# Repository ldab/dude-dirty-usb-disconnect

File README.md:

# dude-dirty-usb-disconnect

USB CDC-ACM uart like controlled USB Hub:

- 1.5A fuse;
- Power switch with overcurrent, undervoltage and overtemperature protection;
- ESD Protection diodes on the USB lines;

## Todo

- [ ] WebBle
- [ ] Web flasher, like: https://esphome.github.io/esp-web-tools/ (does it work over CDC?)
- [ ] Get a PID from https://pid.codes/howto/ (only found how to change TinyUSB PID)
- [ ] There is some overflow around the help print for the `hub_settings`
- [ ] 3D printed case
- [x] `sdkconfig.default` for release with CDC (no jtag)

## Why?

I needed something to remotely disconnect and reconnect an USB device from my workstation, aka managed USB hub, the commercially available options where either [expensive](https://www.usbgear.com/managed-hubs.html) or needed [drivers](https://www.yepkit.com/products/ykush). So the idea here is an device that does not need external power and works as a USB CDC-ACM and one can simply send `hub_ports_off` over the terminal to turns the USB ports off.

## How?

As per USB-C [standard](https://www.usb.org/sites/default/files/USB%20Type-C%20Spec%20R2.0%20-%20August%202019.pdf), if you are bored read section 4.6.2.1, an USB-C source device should at least source 1.5A, as it is written:

  > All exposed USB Type-C Current ports shall have the ability to offer the same power capabilities. 
  > - All ports shall initially offer 1.5 A.

With that being said we can use the HUB with USB2.0 devices (500mA) with no problems. The device monitor the CC pins and it can detect if the source is able to provide the minimum required current (1.5A):

**Table 4-36** indicates that a minimum of 0.7V should be read on CC for a 1.5A capable source, so we should be good with a USB-C to USB-C cable.

If you have an old laptop like me and it does not have an USB-C port, one can override the source check and send `hub_setings override_cc 1` and the HUB ports will be enabled even if the source does not provide enough power. On that case you may experience some weirdness on the final USB device, but hey, if you are here, you should have some idea of what you are doing.

One can also issue `hub_status` and see what the status is, for example:

```
dirty_usb_disconnect> hub_status
FW version: v0.0.1a
Hub is: Enabled
Fault: None
USB Host does not provide 1.5A
```

The CDC-ACM USB driver is based on espressif [example](https://github.com/espressif/esp-idf/tree/v5.2.1/examples/system/console/basic), you will find how it works there... the PID is 0x303A and VID is 0x0009. In case you are building the `debug` version the output will be over the USB-JTAG controller, PID:VID 0x303A:0x1001 (here you can also debug over USB, cool :smile:)

## Firmware

### Available commands

* Type `help` on the terminal

### LED

* Blue - idle, ports off;
* Green - ports on;
* Red - fault;

## Hardware 

- 1.5A fuse;
- [TPS2065C](https://www.ti.com/product/TPS2065C): 1A load, 86mΩ USB power switch with overcurrent, undervoltage and overtemperature protection;
- Device itself draws ~40mA;

- On the boards I made I changed all the resistors to 5.1KOhms for simplicity, the schematic did not update;
- Jumper 1 allows to use the HUB without crystal, saving 0.05USD :smile:;
- Jumper 2 and 3 changes the ADC to channel 2 as the channel 1 has a boot glitch (it should be ok). Bear in mind that ADC2 does not work with WiFi (rtfm);

## Note

- The hub controller datasheet indicates a internal pullup on RST, but it seems something is going on there, so next revision needs an external pull up, for now: https://github.com/ldab/dude-dirty-usb-disconnect/blob/4d217c8b5ad06fc77f75e4162ce3a6a554248eb0/components/app_hub_control/app_hub_control.c#L406

## Outro

- Some 3D models from: www.3dcontentcentral.com

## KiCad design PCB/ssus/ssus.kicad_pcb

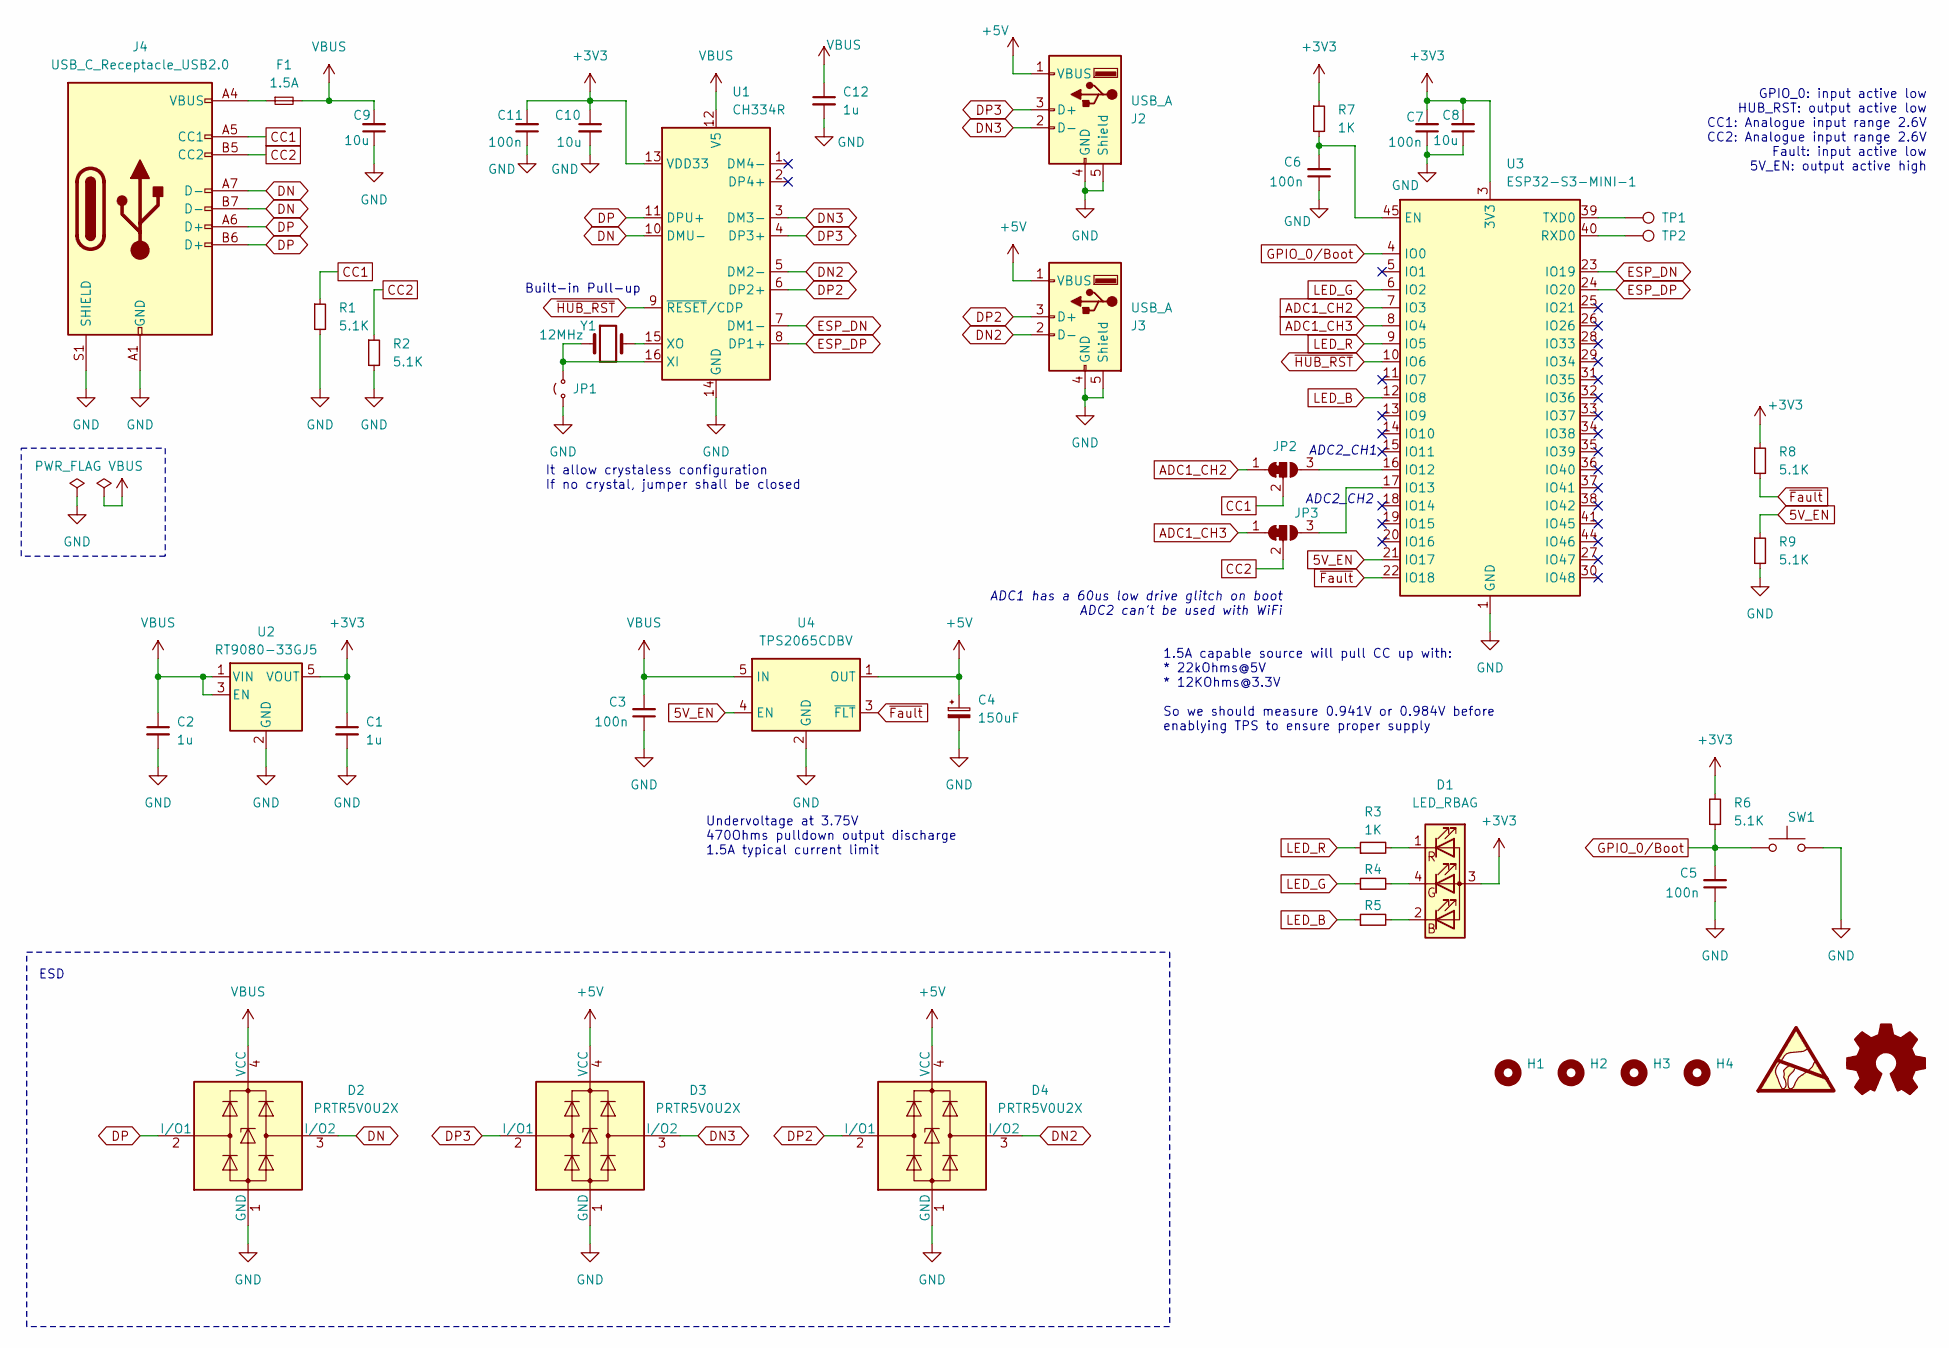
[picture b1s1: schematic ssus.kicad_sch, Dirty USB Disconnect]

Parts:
C1, C2, C12: 1u; C_0603_1608Metric; LCSC C1592
C3, C5, C6, C7, C11: 100n; C_0603_1608Metric; LCSC C338036
C4: 150uF; C_Elec_6.3x5.4; LCSC C2895744
C8, C9, C10: 10u; C_0603_1608Metric; LCSC C87152
D1: LED_RBAG; LED_Cree-PLCC4_2x2mm_CW; LCSC C108793
D2, D3, D4: PRTR5V0U2X; SOT-143; LCSC C12333
F1: 1.5A; Fuse_1206_3216Metric; LCSC C89655
H1, H2, H3, H4: MountingHole; MountingHole_2.1mm
J2, J3: USB_A; USB_A_TE_292303-7_Horizontal; LCSC C42641
J4: USB_C_Receptacle_USB2.0; USB_C_Receptacle_HRO_TYPE-C-31-M-12; LCSC C319148
JP1: 2; SolderJumper-2_P1.3mm_Open_RoundedPad1.0x1.5mm
JP2, JP3: 3; SolderJumper-3_P1.3mm_Bridged12_RoundedPad1.0x1.5mm
R1, R2, R6, R8, R9: 5.1K; R_0603_1608Metric; LCSC C14677
R3, R4, R5, R7: 1K; R_0603_1608Metric; LCSC C384295
SW1: SW_Push; SW_Push_1P1T_NO_CK_KMR2; LCSC C128941
TP1, TP2: TestPoint; TestPoint_Pad_D1.5mm
U1: CH334R; QSOP-16_3.9x4.9mm_P0.635mm; LCSC C4154405
U2: RT9080-33GJ5; SOT-23-5; LCSC C841192
U3: ESP32-S3-MINI-1; ESP32-S2-MINI-1; LCSC C2913206
U4: TPS2065CDBV; SOT-23-5; LCSC C353882
Y1: 12MHz; Oscillator_SMD_ECS_2520MV-xxx-xx-4Pin_2.5x2.0mm; LCSC C21714041

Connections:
5V_EN: R9.1, U3.21 (IO17), U4.4 (EN)
+3V3: C1.1, C7.2, C8.2, C10.1, C11.2, D1.3 (A), R6.2, R7.1, R8.1, U1.13 (VDD33), U2.5 (VOUT), U3.3 (3V3)
+5V: C4.1, D3.4 (VCC), D4.4 (VCC), J2.1 (VBUS), J3.1 (VBUS), U4.1 (OUT)
ADC1_CH2: JP2.1 (A), U3.7 (IO3)
ADC1_CH3: JP3.1 (A), U3.8 (IO4)
CC1: J4.A5 (CC1), JP2.2 (C), R1.1
CC2: J4.B5 (CC2), JP3.2 (C), R2.1
DN: D2.3 (I/O2), J4.A7 (D-), J4.B7 (D-), U1.10 (DMU-)
DN2: D4.3 (I/O2), J3.2 (D-), U1.5 (DM2-)
DN3: D3.3 (I/O2), J2.2 (D-), U1.3 (DM3-)
DP: D2.2 (I/O1), J4.A6 (D+), J4.B6 (D+), U1.11 (DPU+)
DP2: D4.2 (I/O1), J3.3 (D+), U1.6 (DP2+)
DP3: D3.2 (I/O1), J2.3 (D+), U1.4 (DP3+)
ESP_DN: U1.7 (DM1-), U3.23 (IO19)
ESP_DP: U1.8 (DP1+), U3.24 (IO20)
GND: C1.2, C2.2, C3.1, C4.2, C5.1, C6.1, C7.1, C8.1, C9.1, C10.2, C11.1, C12.2, D2.1 (GND), D3.1 (GND), D4.1 (GND), J2.4 (GND), J2.5 (Shield), J3.4 (GND), J3.5 (Shield), J4.A1 (GND), J4.A12 (GND), J4.B1 (GND), J4.B12 (GND), J4.S1 (SHIELD), JP1.1 (A), R1.2, R2.2, R9.2, SW1.2, U1.14 (GND), U2.2 (GND), U3.1 (GND), U3.2 (GND), U3.42 (GND), U3.43 (GND), U3.46 (GND), U3.47 (GND), U3.48 (GND), U3.49 (GND), U3.50 (GND), U3.51 (GND), U3.52 (GND), U3.53 (GND), U3.54 (GND), U3.55 (GND), U3.56 (GND), U3.57 (GND), U3.58 (GND), U3.59 (GND), U3.60 (GND), U3.61 (GND), U3.62 (GND), U3.63 (GND), U3.64 (GND), U3.65 (GND), U4.2 (GND)
GPIO_0/Boot: C5.2, R6.1, SW1.1, U3.4 (IO0)
LED_B: R5.1, U3.12 (IO8)
LED_G: R4.1, U3.6 (IO2)
LED_R: R3.1, U3.9 (IO5)
unnamed: D1.2 (BK), R5.2
unnamed: D1.4 (GK), R4.2
unnamed: D1.1 (RK), R3.2
unnamed: F1.1, J4.A4 (VBUS), J4.A9 (VBUS), J4.B4 (VBUS), J4.B9 (VBUS)
unnamed: JP1.2 (B), U1.16 (XI), Y1.1
unnamed: JP2.3 (B), U3.16 (IO12)
unnamed: JP3.3 (B), U3.17 (IO13)
unnamed: U1.15 (XO), Y1.2
unnamed: C6.2, R7.2, U3.45 (EN)
unnamed: TP2.1, U3.40 (RXD0)
unnamed: TP1.1, U3.39 (TXD0)
VBUS: C2.1, C3.2, C9.2, C12.1, D2.4 (VCC), F1.2, U1.12 (V5), U2.1 (VIN), U2.3 (EN), U4.5 (IN)
~Fault: R8.2, U3.22 (IO18), U4.3 (~FLT)
~HUB_RST: U1.9 (~RESET/CDP), U3.10 (IO6)

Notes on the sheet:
GPIO_0: input active low HUB_RST: output active low CC1: Analogue input range 2.6V CC2: Analogue input range 2.6V Fault: input active low 5V_EN: output active high
ADC2_CH1
It allow crystaless configuration If no crystal, jumper shall be closed
ADC2_CH2
1.5A capable source will pull CC up with: * 22kOhms@5V * 12KOhms@3.3V So we should measure 0.941V or 0.984V before enablying TPS to ensure proper supply
Built-in Pull-up
ESD
Undervoltage at 3.75V 470Ohms pulldown output discharge 1.5A typical current limit
ADC1 has a 60us low drive glitch on boot ADC2 can't be used with WiFi

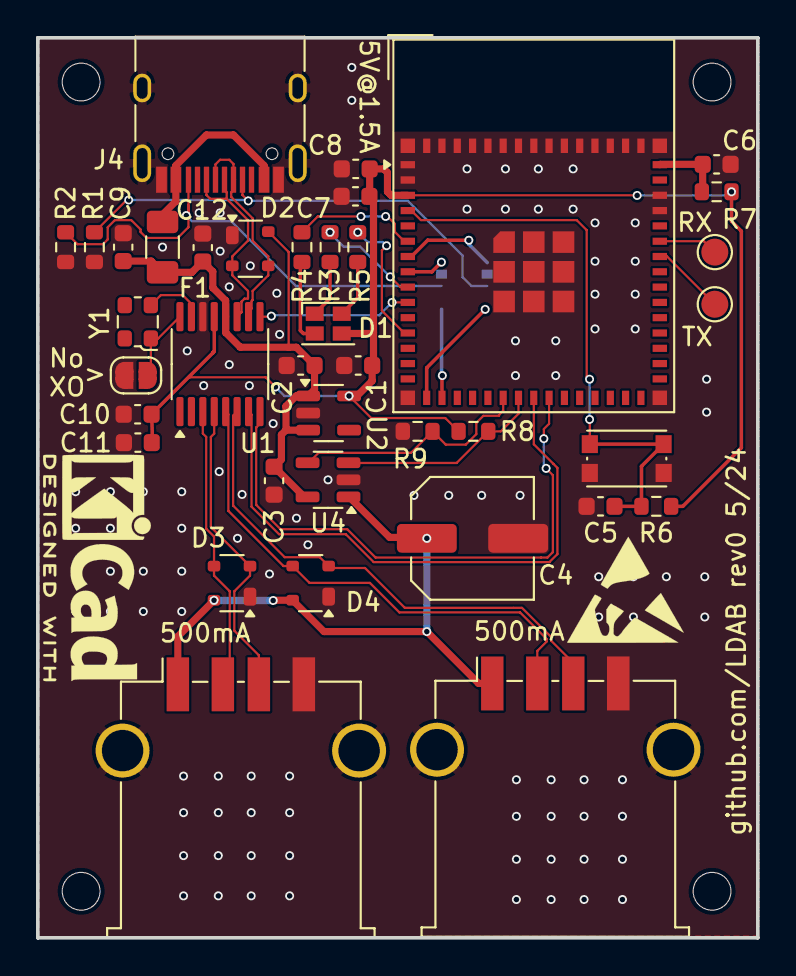
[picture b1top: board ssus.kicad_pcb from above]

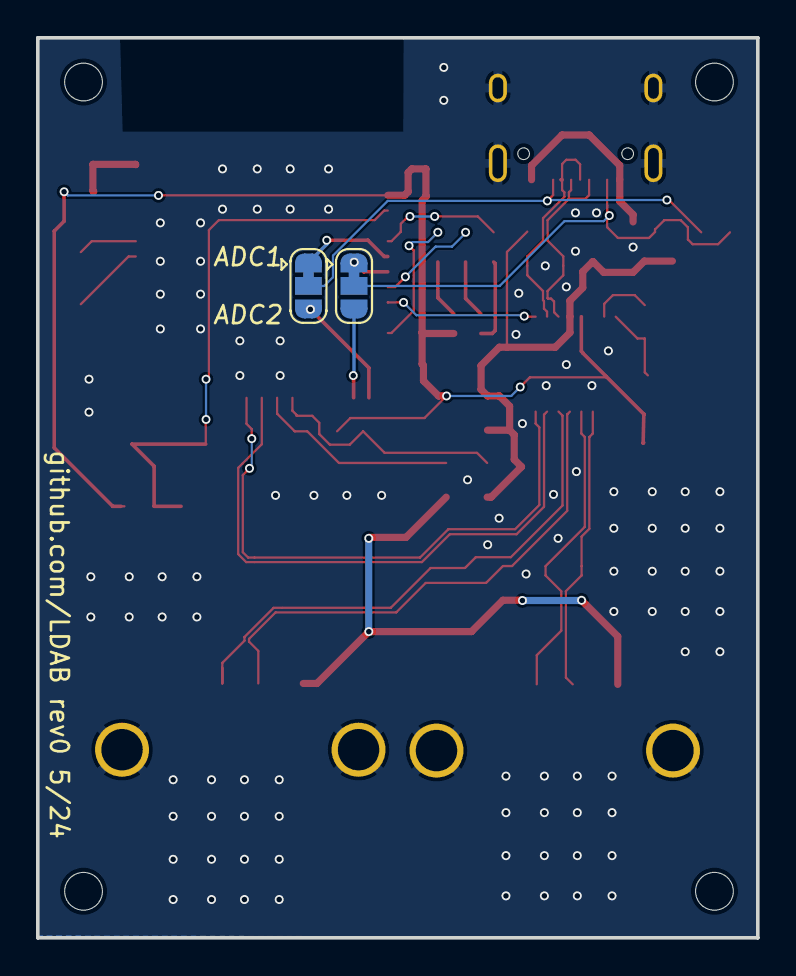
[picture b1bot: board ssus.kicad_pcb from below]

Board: 2 copper layers, 40.0 x 50.0 mm, 44 parts (2 on the bottom side), 34 nets.

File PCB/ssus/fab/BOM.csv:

"Reference","Value","Footprint","Qty","LCSC","DNP"
"C1,C2,C12","1u","Capacitor_SMD:C_0603_1608Metric","3","C1592",""
"C3,C5,C6,C7,C11","100n","Capacitor_SMD:C_0603_1608Metric","5","C338036",""
"C4","150uF","Capacitor_SMD:C_Elec_6.3x5.4","1","C2895744",""
"C8,C9,C10","10u","Capacitor_SMD:C_0603_1608Metric","3","C87152",""
"D1","LED_RBAG","LED_SMD:LED_Cree-PLCC4_2x2mm_CW","1","C108793",""
"D2,D3,D4","PRTR5V0U2X","Package_TO_SOT_SMD:SOT-143","3","C12333",""
"F1","1.5A","Fuse:Fuse_1206_3216Metric","1","C89655",""
"J2,J3","USB_A","Connector_USB:USB_A_TE_292303-7_Horizontal","2","C42641",""
"J4","USB_C_Receptacle_USB2.0","Connector_USB:USB_C_Receptacle_HRO_TYPE-C-31-M-12","1","C319148",""
"JP1","2","Jumper:SolderJumper-2_P1.3mm_Open_RoundedPad1.0x1.5mm","1","",""
"R1,R2,R6,R8,R9","5.1K","Resistor_SMD:R_0603_1608Metric","5","C14677",""
"R3,R4,R5,R7","1K","Resistor_SMD:R_0603_1608Metric","4","C384295",""
"SW1","SW_Push","Button_Switch_SMD:SW_Push_1P1T_NO_CK_KMR2","1","C128941",""
"TP1,TP2","TestPoint","TestPoint:TestPoint_Pad_D1.5mm","2","",""
"U1","CH334R","Package_SO:QSOP-16_3.9x4.9mm_P0.635mm","1","C4154405",""
"U2","RT9080-33GJ5","Package_TO_SOT_SMD:SOT-23-5","1","C841192",""
"U3","ESP32-S3-MINI-1","RF_Module:ESP32-S2-MINI-1","1","C2913206",""
"U4","TPS2065CDBV","Package_TO_SOT_SMD:SOT-23-5","1","C353882",""
"Y1","12MHz","Oscillator:Oscillator_SMD_ECS_2520MV-xxx-xx-4Pin_2.5x2.0mm","1","C21714041",""

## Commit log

2024-05-05 start
2024-05-25 update docs

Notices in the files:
README.md:
License: WTFPL
